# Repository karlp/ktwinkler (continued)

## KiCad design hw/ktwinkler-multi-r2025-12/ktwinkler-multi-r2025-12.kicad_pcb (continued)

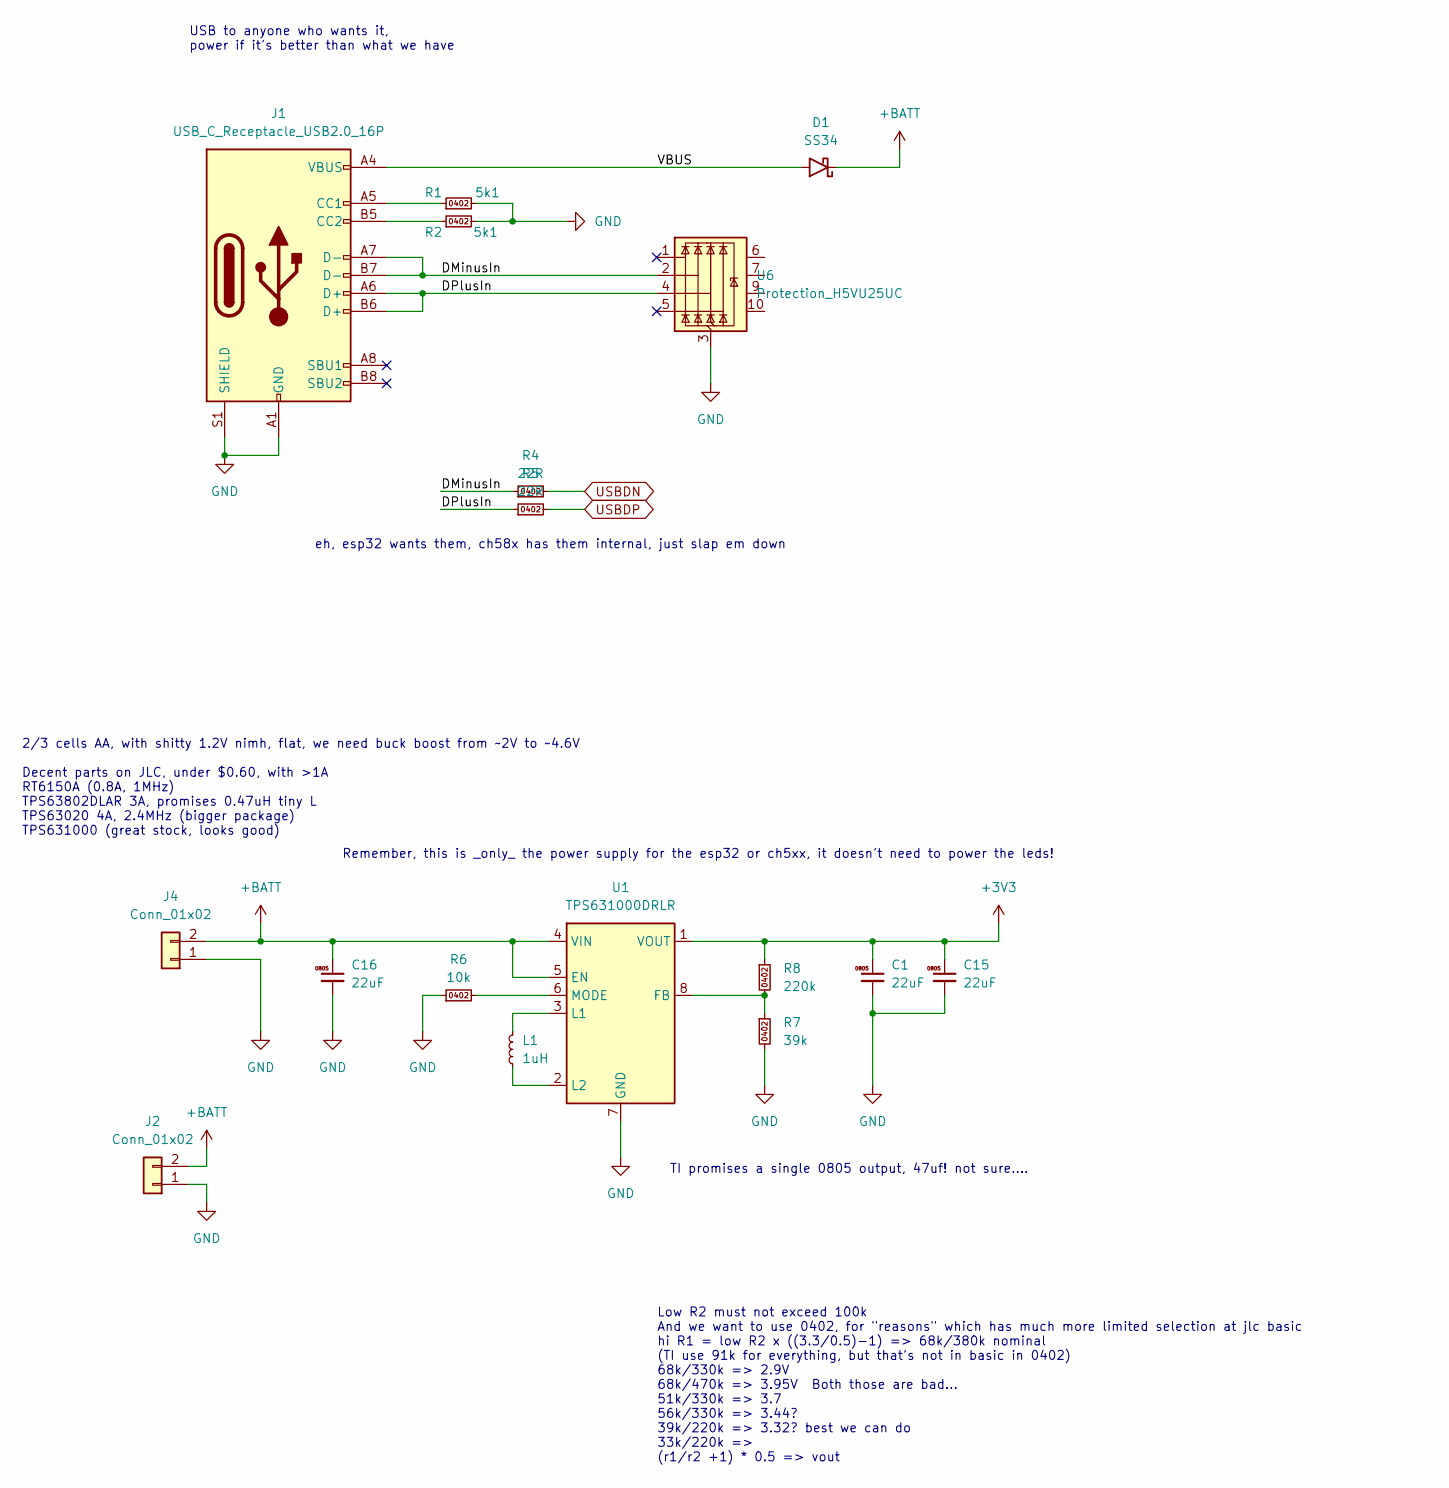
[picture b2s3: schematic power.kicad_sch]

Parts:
C1, C15, C16: 22uF; C_0805_2012Metric; MPN CL21A226MAQNNNE; LCSC Part # C45783
D1: SS34; D_SMA; MPN SS34; LCSC Part # C8678
J1: USB_C_Receptacle_USB2.0_16P; USB_C_Receptacle_GCT_USB4105-xx-A_16P_TopMnt_Horizontal; MPN GT-USB-7010ASV; LCSC Part # C2988369
J2: Conn_01x02; PinHeader_1x02_P2.54mm_Vertical
J4: Conn_01x02; PhoenixContact_MC_1,5_2-G-3.5_1x02_P3.50mm_Horizontal; MPN WJ15EDGVC-3.81-2P; LCSC Part # C8387
L1: 1uH; L_1206_3216Metric; MPN CMP321609UD1R0MT; LCSC Part # C139248
R1, R2: 5k1; R_0402_1005Metric; MPN 0402WGF5101TCE; LCSC Part # C25905
R4, R5: 22R; R_0402_1005Metric; MPN 0402WGF220JTCE; LCSC Part # C25092
R6: 10k; R_0402_1005Metric; MPN 0402WGF1002TCE; LCSC Part # C25744
R7: 39k; R_0402_1005Metric; MPN 0402WGF3902TCE; LCSC Part # C25783
R8: 220k; R_0402_1005Metric; MPN 0402WGF2203TCE; LCSC Part # C25767
U1: TPS631000DRLR; SOT-583-8; MPN TPS631000DRLR; LCSC Part # C5219190
U6: Protection_H5VU25UC; Diodes_UDFN-10_1.0x2.5mm_P0.5mm; MPN H5VU25UC; jlcbasic preferred

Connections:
+3V3: C1.1, C15.1, R8.1, U1.1 (VOUT); also elsewhere on the board
+BATT: C16.1, D1.1 (K), J2.2, J4.2, U1.4 (VIN), U1.5 (EN); also elsewhere on the board
/power/DMinusIn: J1.A7 (D-), J1.B7 (D-), R4.1, U6.2 (I/O2)
/power/DPlusIn: J1.A6 (D+), J1.B6 (D+), R5.1, U6.4 (I/O3)
/power/VBUS: D1.2 (A), J1.A4 (VBUS), J1.A9 (VBUS), J1.B4 (VBUS), J1.B9 (VBUS)
GND: C1.2, C15.2, C16.2, J1.A1 (GND), J1.A12 (GND), J1.B1 (GND), J1.B12 (GND), J1.S1 (SHIELD), J2.1, J4.1, R1.2, R2.2, R6.1, R7.2, U1.7 (GND), U6.3 (GND), U6.8 (GND); also elsewhere on the board
unnamed: J1.A5 (CC1), R1.1
unnamed: J1.B5 (CC2), R2.1
unnamed: R7.1, R8.2, U1.8 (FB)
unnamed: L1.2, U1.3 (L1)
unnamed: L1.1, U1.2 (L2)
unnamed: R6.2, U1.6 (MODE)
USBDN: R4.2; also elsewhere on the board
USBDP: R5.2; also elsewhere on the board

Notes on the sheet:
Low R2 must not exceed 100k And we want to use 0402, for "reasons" which has much more limited selection at jlc basic hi R1 = low R2 x ((3.3/0.5)-1) => 68k/380k nominal (TI use 91k for everything, but that's not in basic in 0402) 68k/330k => 2.9V 68k/470k => 3.95V Both those are bad... 51k/330k => 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
USB to anyone who wants it, power if it's better than what we have
2/3 cells AA, with shitty 1.2V nimh, flat, we need buck boost from ~2V to ~4.6V Decent parts on JLC, under $0.60, with >1A RT6150A (0.8A, 1MHz) TPS63802DLAR 3A, promises 0.47uH tiny L TPS63020 4A, 2.4MHz (bigger package) TPS631000 (great stock, looks good)
Remember, this is _only_ the power supply for the esp32 or ch5xx, it doesn't need to power the leds!
eh, esp32 wants them, ch58x has them internal, just slap em down
TI promises a single 0805 output, 47uf! not sure....

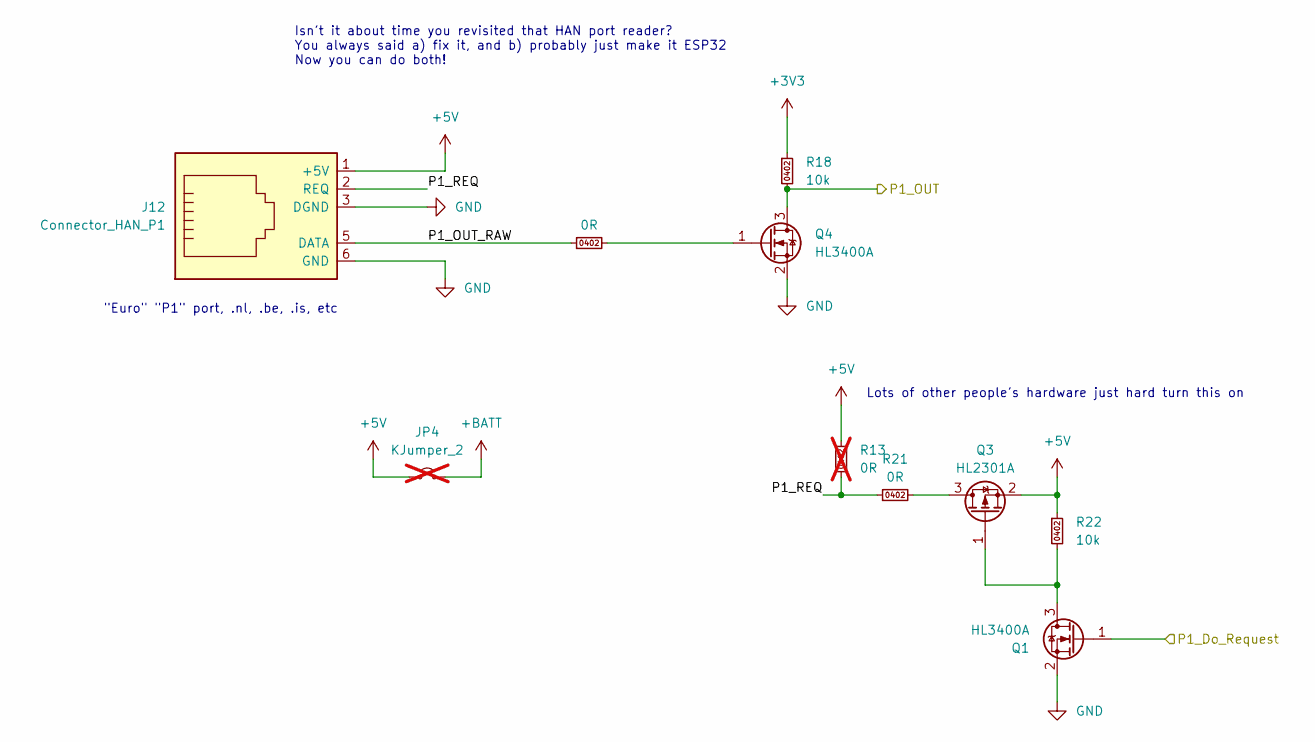
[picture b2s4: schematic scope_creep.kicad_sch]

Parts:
J12: Connector_HAN_P1; RJ25_Wayconn_MJEA-660X1_Horizontal; MPN R-RJ11R06P-A801
JP4: KJumper_2; TestPoint_2Pads_Pitch2.54mm_Drill0.8mm; not fitted
Q1, Q4: HL3400A; SOT-23; MPN HL3400A; LCSC Part # C7420348
Q3: HL2301A; SOT-23; jlcbasic preferred
R13: 0R; R_0402_1005Metric; MPN 0402WGF0000TCE; LCSC Part # C17168; not fitted
R17, R21: 0R; R_0402_1005Metric; MPN 0402WGF0000TCE; LCSC Part # C17168
R18, R22: 10k; R_0402_1005Metric; MPN 0402WGF1002TCE; LCSC Part # C25744

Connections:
+3V3: R18.1; also elsewhere on the board
+5V: J12.1 (+5V), JP4.1 (A), Q3.2 (S), R13.2, R22.1
+BATT: JP4.2 (B); also elsewhere on the board
/ScopeCreep/P1_OUT_RAW: J12.5 (DATA), R17.1
/ScopeCreep/P1_REQ: J12.2 (REQ), R13.1, R21.1
/ch584/PWM3: Q4.3 (D), R18.2; also elsewhere on the board
/ch584/PWM5: Q1.1 (G); also elsewhere on the board
GND: J12.3 (DGND), J12.6 (GND), Q1.2 (S), Q4.2 (S); also elsewhere on the board
unnamed: Q1.3 (D), Q3.1 (G), R22.2
unnamed: Q3.3 (D), R21.2
unnamed: Q4.1 (G), R17.2

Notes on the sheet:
Lots of other people's hardware just hard turn this on
Isn't it about time you revisited that HAN port reader? You always said a) fix it, and b) probably just make it ESP32 Now you can do both!
"Euro" "P1" port, .nl, .be, .is, etc

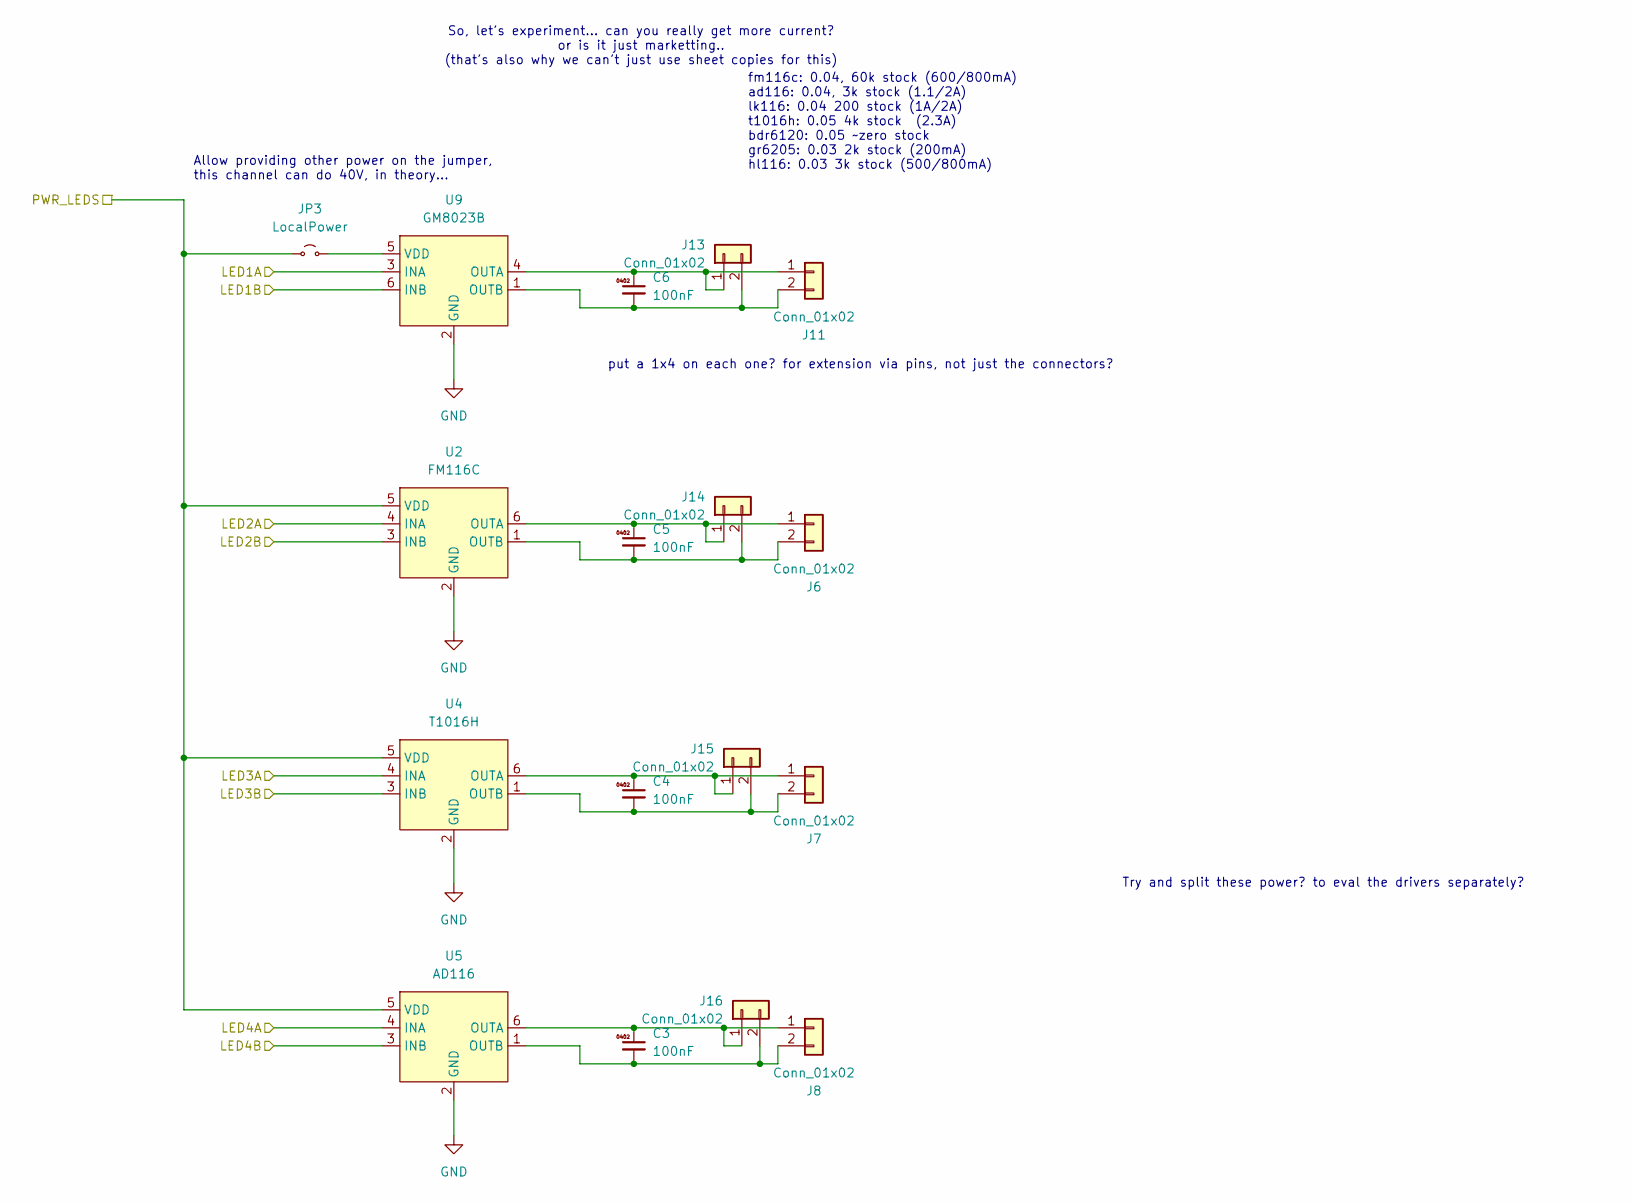
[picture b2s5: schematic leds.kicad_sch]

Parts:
C3, C4, C5, C6: 100nF; C_0402_1005Metric; MPN CL05B104KO5NNNC; LCSC Part # C1525
J6, J7, J8: Conn_01x02; PhoenixContact_MC_1,5_2-G-3.5_1x02_P3.50mm_Horizontal; MPN WJ15EDGVC-3.81-2P; LCSC Part # C8387
J11: Conn_01x02; PhoenixContact_MC_1,5_2-G-3.5_1x02_P3.50mm_Horizontal; MPN WJ15EDGRC-3.81-2P; LCSC Part # C8387
J13, J14, J15, J16: Conn_01x02; TestPoint_2Pads_Pitch2.54mm_Drill0.8mm
JP3: LocalPower; TestPoint_2Pads_Pitch2.54mm_Drill0.8mm
U2: FM116C; SOT-23-6; MPN FM116C; LCSC Part # C2802264
U4: T1016H; SOT-23-6; MPN T1016H; LCSC Part # C5142991
U5: AD116; SOT-23-6; MPN AD116; LCSC Part # C7463412
U9: GM8023B; SOT-23-6; MPN GM8023B; LCSC Part # C269871

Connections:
+BATT: JP3.1 (A), U2.5 (VDD), U4.5 (VDD), U5.5 (VDD); also elsewhere on the board
/ch584/PWM1: U9.3 (INA); also elsewhere on the board
/ch584/PWM2: U9.6 (INB); also elsewhere on the board
/ch584/PWM3: U2.4 (INA); also elsewhere on the board
/ch584/PWM4: U2.3 (INB); also elsewhere on the board
/ch584/PWM5: U4.4 (INA); also elsewhere on the board
/esp32/PWM7: U5.4 (INA); also elsewhere on the board
/esp32/PWM8: U5.3 (INB); also elsewhere on the board
GND: U2.2 (GND), U4.2 (GND), U5.2 (GND), U9.2 (GND); also elsewhere on the board
unnamed: C6.1, J11.1, J13.1, U9.4 (OUTA)
unnamed: C6.2, J11.2, J13.2, U9.1 (OUTB)
unnamed: C5.1, J6.1, J14.1, U2.6 (OUTA)
unnamed: C5.2, J6.2, J14.2, U2.1 (OUTB)
unnamed: C4.1, J7.1, J15.1, U4.6 (OUTA)
unnamed: C4.2, J7.2, J15.2, U4.1 (OUTB)
unnamed: C3.1, J8.1, J16.1, U5.6 (OUTA)
unnamed: C3.2, J8.2, J16.2, U5.1 (OUTB)
unnamed: JP3.2 (B), U9.5 (VDD)
RESET_CH5x: U4.3 (INB); also elsewhere on the board

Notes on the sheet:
So, let's experiment... can you really get more current? or is it just marketting.. (that's also why we can't just use sheet copies for this)
put a 1x4 on each one? for extension via pins, not just the connectors?
Allow providing other power on the jumper, this channel can do 40V, in theory...
Try and split these power? to eval the drivers separately?
fm116c: 0.04, 60k stock (600/800mA) ad116: 0.04, 3k stock (1.1/2A) lk116: 0.04 200 stock (1A/2A) t1016h: 0.05 4k stock (2.3A) bdr6120: 0.05 ~zero stock gr6205: 0.03 2k stock (200mA) hl116: 0.03 3k stock (500/800mA)

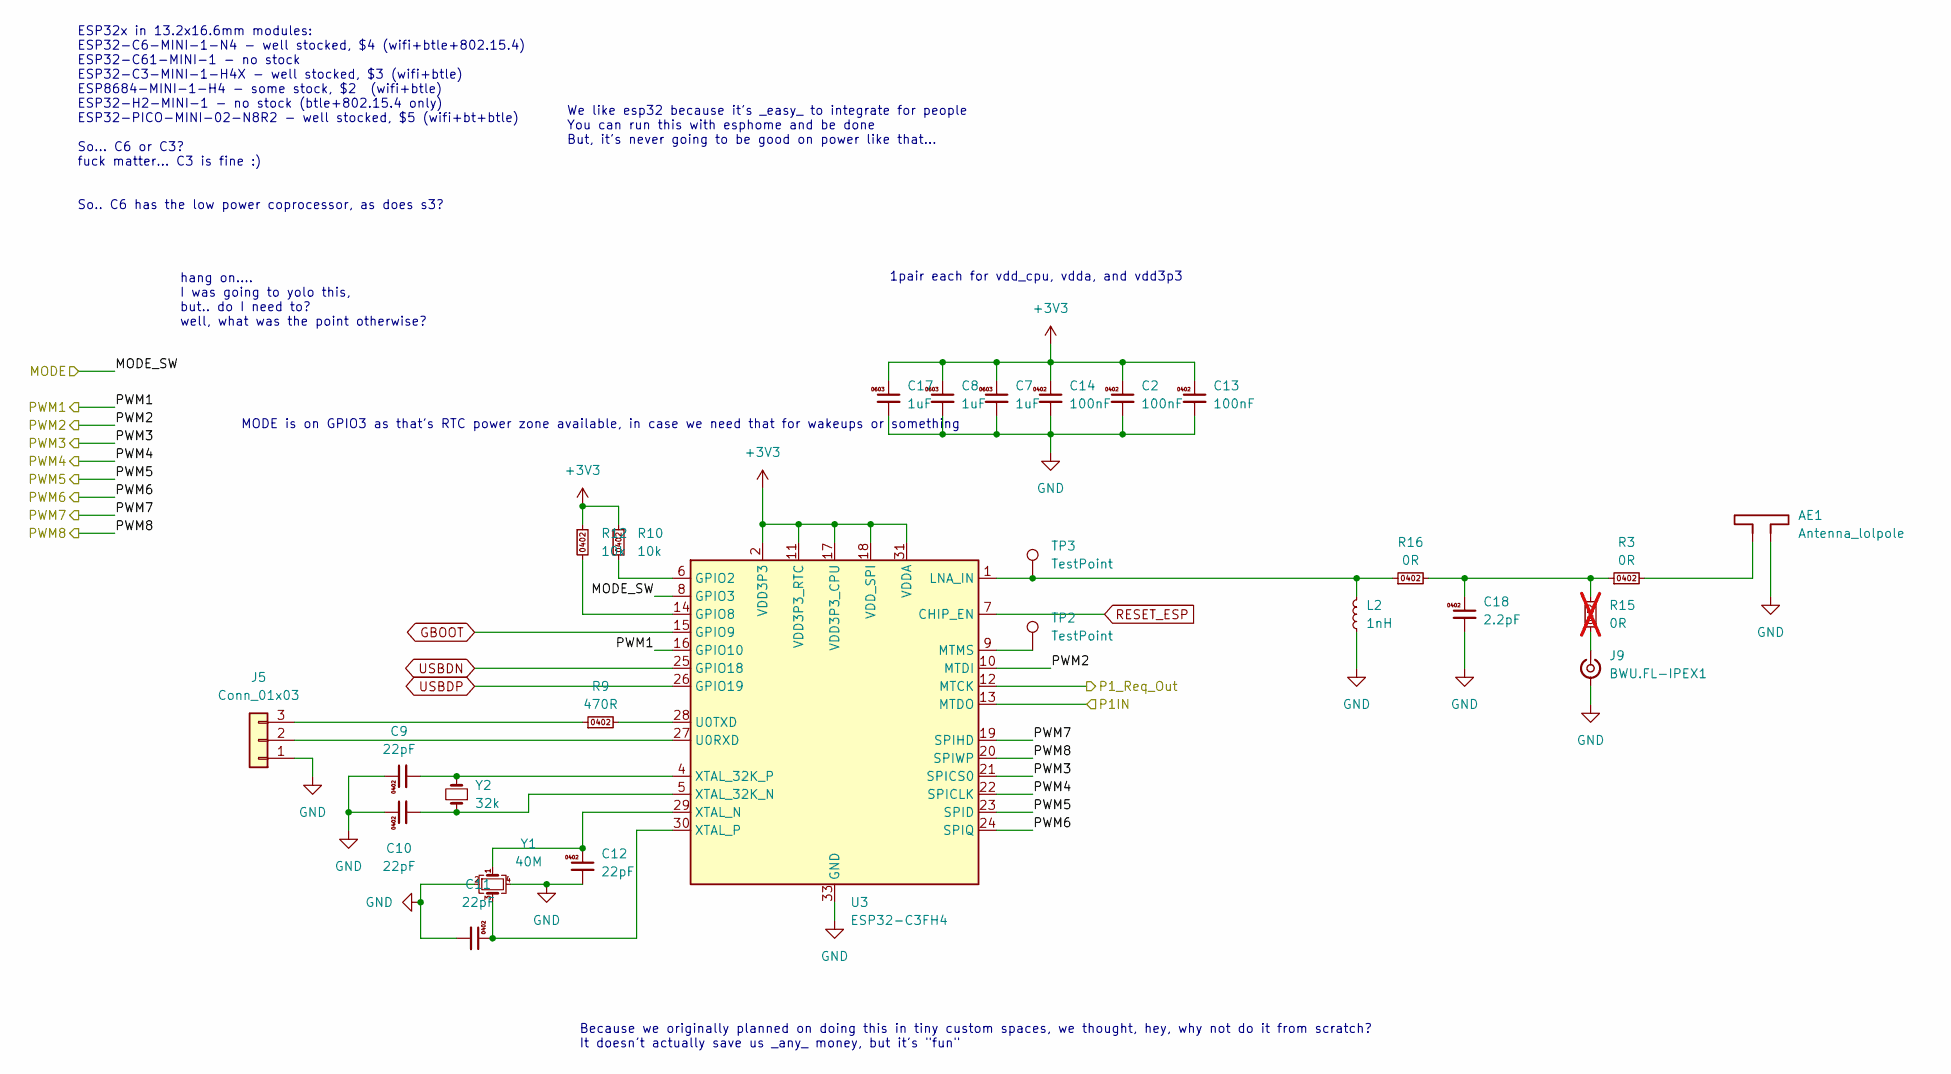
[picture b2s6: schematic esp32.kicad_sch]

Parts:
AE1: Antenna_lolpole; ANT-YOLOPOLE
C2, C13, C14: 100nF; C_0402_1005Metric; MPN CL05B104KO5NNNC; LCSC Part # C1525
C7, C8, C17: 1uF; C_0603_1608Metric; MPN CL10A105KB8NNNC; LCSC Part # C15849
C9, C10, C11, C12: 22pF; C_0402_1005Metric; MPN 0402CG220J500NT; LCSC Part # C1555
C18: 2.2pF; C_0402_1005Metric; MPN 0402CG2R2C500NT; LCSC Part # C1559
J5: Conn_01x03; PinHeader_1x03_P2.54mm_Vertical
J9: BWU.FL-IPEX1; U.FL_Hirose_U.FL-R-SMT-1_Vertical; MPN BWU.FL-IPEX1; LCSC Part # C5137195
L2: 1nH; L_0402_1005Metric; MPN LQG15HS1N0S02D; LCSC Part # C18222
R3, R16: 0R; R_0402_1005Metric; MPN 0402WGF0000TCE; LCSC Part # C17168
R9: 470R; R_0402_1005Metric; MPN 0402WGF4700TCE; LCSC Part # C25117
R10, R12: 10k; R_0402_1005Metric; MPN 0402WGF1002TCE; LCSC Part # C25744
R15: 0R; R_0402_1005Metric; MPN 0402WGF0000TCE; LCSC Part # C17168; not fitted
TP2: TestPoint; TestPoint_THTPad_D1.0mm_Drill0.5mm
TP3: TestPoint; TestPoint_Pad_D1.0mm
U3: ESP32-C3FH4; QFN-32-1EP_5x5mm_P0.5mm_EP3.7x3.7mm; MPN ESP32-C3FH4; LCSC Part # C2858491
Y1: 40M; Crystal_SMD_2016-4Pin_2.0x1.6mm; MPN TAXM40M4ZHBCDT2T; LCSC Part # C424432
Y2: 32k; Crystal_SMD_3215-2Pin_3.2x1.5mm; MPN Q13FC13500004; LCSC Part # C32346

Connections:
+3V3: C2.1, C7.1, C8.1, C13.1, C14.1, C17.1, R10.1, R12.1, U3.2 (VDD3P3), U3.3 (VDD3P3), U3.11 (VDD3P3_RTC), U3.17 (VDD3P3_CPU), U3.18 (VDD_SPI), U3.31 (VDDA), U3.32 (VDDA); also elsewhere on the board
/MODE: U3.8 (GPIO3); also elsewhere on the board
/ch584/PWM1: U3.16 (GPIO10); also elsewhere on the board
/ch584/PWM2: U3.10 (MTDI); also elsewhere on the board
/ch584/PWM3: U3.13 (MTDO), U3.21 (SPICS0); also elsewhere on the board
/ch584/PWM4: U3.22 (SPICLK); also elsewhere on the board
/ch584/PWM5: U3.12 (MTCK), U3.23 (SPID); also elsewhere on the board
/esp32/PWM7: U3.19 (SPIHD); also elsewhere on the board
/esp32/PWM8: U3.20 (SPIWP); also elsewhere on the board
GBOOT: U3.15 (GPIO9); also elsewhere on the board
GND: AE1.2, C2.2, C7.2, C8.2, C9.1, C10.1, C11.2, C12.2, C13.2, C14.2, C17.2, C18.2, J5.1, J9.2 (Ext), L2.1, U3.33 (GND), Y1.2, Y1.4; also elsewhere on the board
unnamed: AE1.1, R3.2
unnamed: C18.1, R3.1, R15.2, R16.2
unnamed: J5.2, U3.27 (U0RXD)
unnamed: J5.3, R9.1
unnamed: J9.1 (In), R15.1
unnamed: R10.2, U3.6 (GPIO2)
unnamed: R12.2, U3.14 (GPIO8)
unnamed: L2.2, R16.1, TP3.1 (1_1), U3.1 (LNA_IN)
unnamed: TP2.1 (1_1), U3.9 (MTMS)
unnamed: R9.2, U3.28 (U0TXD)
unnamed: C10.2, U3.5 (XTAL_32K_N), Y2.1
unnamed: C9.2, U3.4 (XTAL_32K_P), Y2.2
unnamed: C12.1, U3.29 (XTAL_N), Y1.1
unnamed: C11.1, U3.30 (XTAL_P), Y1.3
RESET_CH5x: U3.24 (SPIQ); also elsewhere on the board
RESET_ESP: U3.7 (CHIP_EN); also elsewhere on the board
USBDN: U3.25 (GPIO18); also elsewhere on the board
USBDP: U3.26 (GPIO19); also elsewhere on the board

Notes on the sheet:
hang on.... I was going to yolo this, but.. do I need to? well, what was the point otherwise?
MODE is on GPIO3 as that's RTC power zone available, in case we need that for wakeups or something
ESP32x in 13.2x16.6mm modules: ESP32-C6-MINI-1-N4 - well stocked, $4 (wifi+btle+802.15.4) ESP32-C61-MINI-1 - no stock ESP32-C3-MINI-1-H4X - well stocked, $3 (wifi+btle) ESP8684-MINI-1-H4 - some stock, $2 (wifi+btle) ESP32-H2-MINI-1 - no stock (btle+802.15.4 only) ESP32-PICO-MINI-02-N8R2 - well stoc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
Because we originally planned on doing this in tiny custom spaces, we thought, hey, why not do it from scratch? It doesn't actually save us _any_ money, but it's "fun"
We like esp32 because it's _easy_ to integrate for people You can run this with esphome and be done But, it's never going to be good on power like that...
1pair each for vdd_cpu, vdda, and vdd3p3

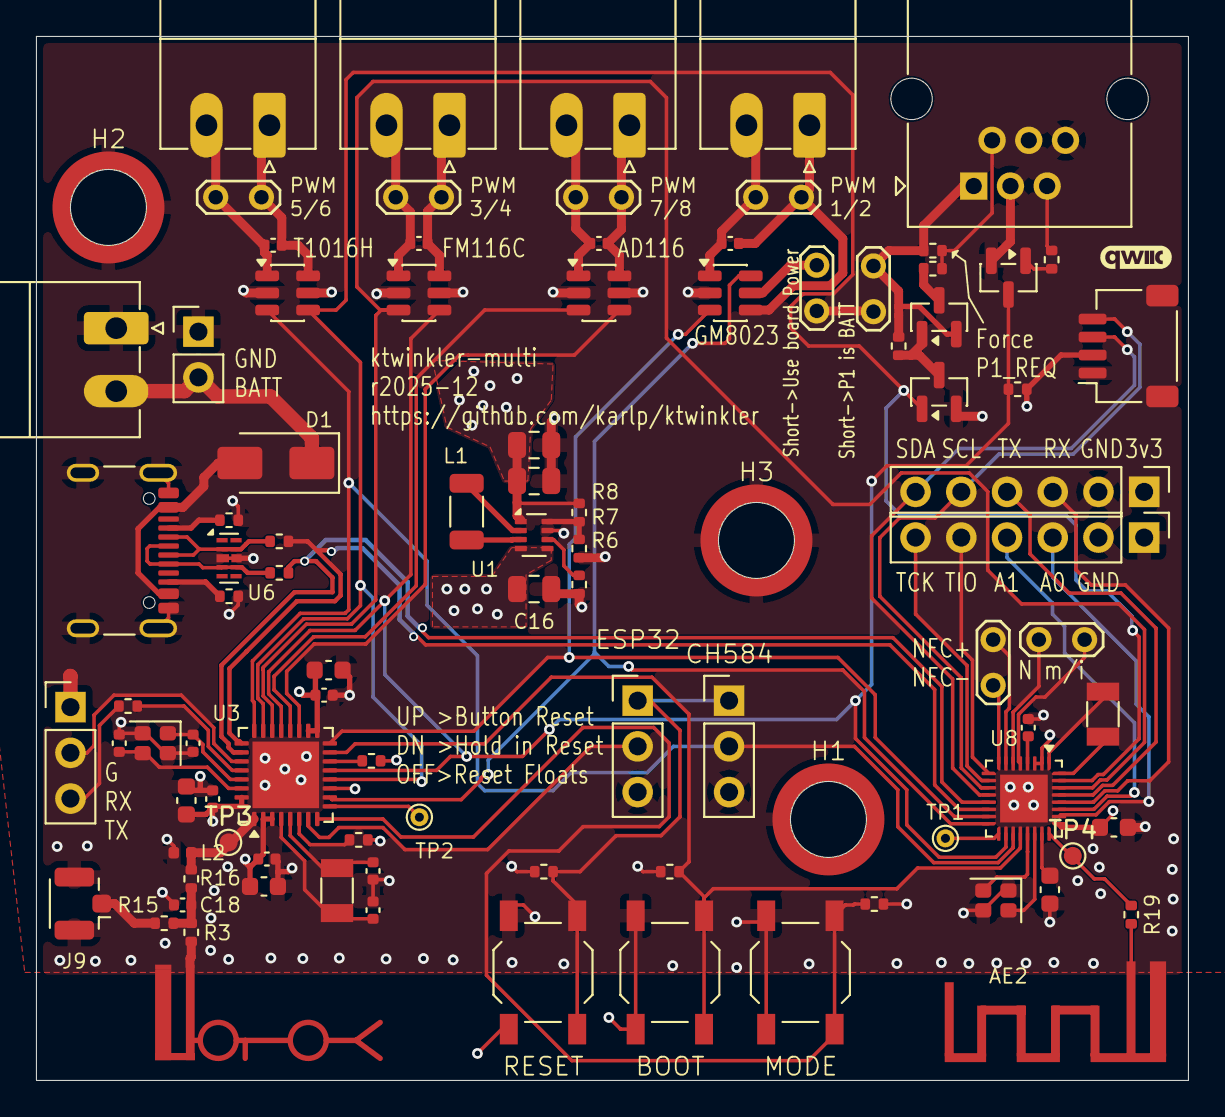
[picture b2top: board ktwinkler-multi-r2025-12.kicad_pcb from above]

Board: 4 copper layers, 64.0 x 58.0 mm, 97 parts (0 on the bottom side), 77 nets.

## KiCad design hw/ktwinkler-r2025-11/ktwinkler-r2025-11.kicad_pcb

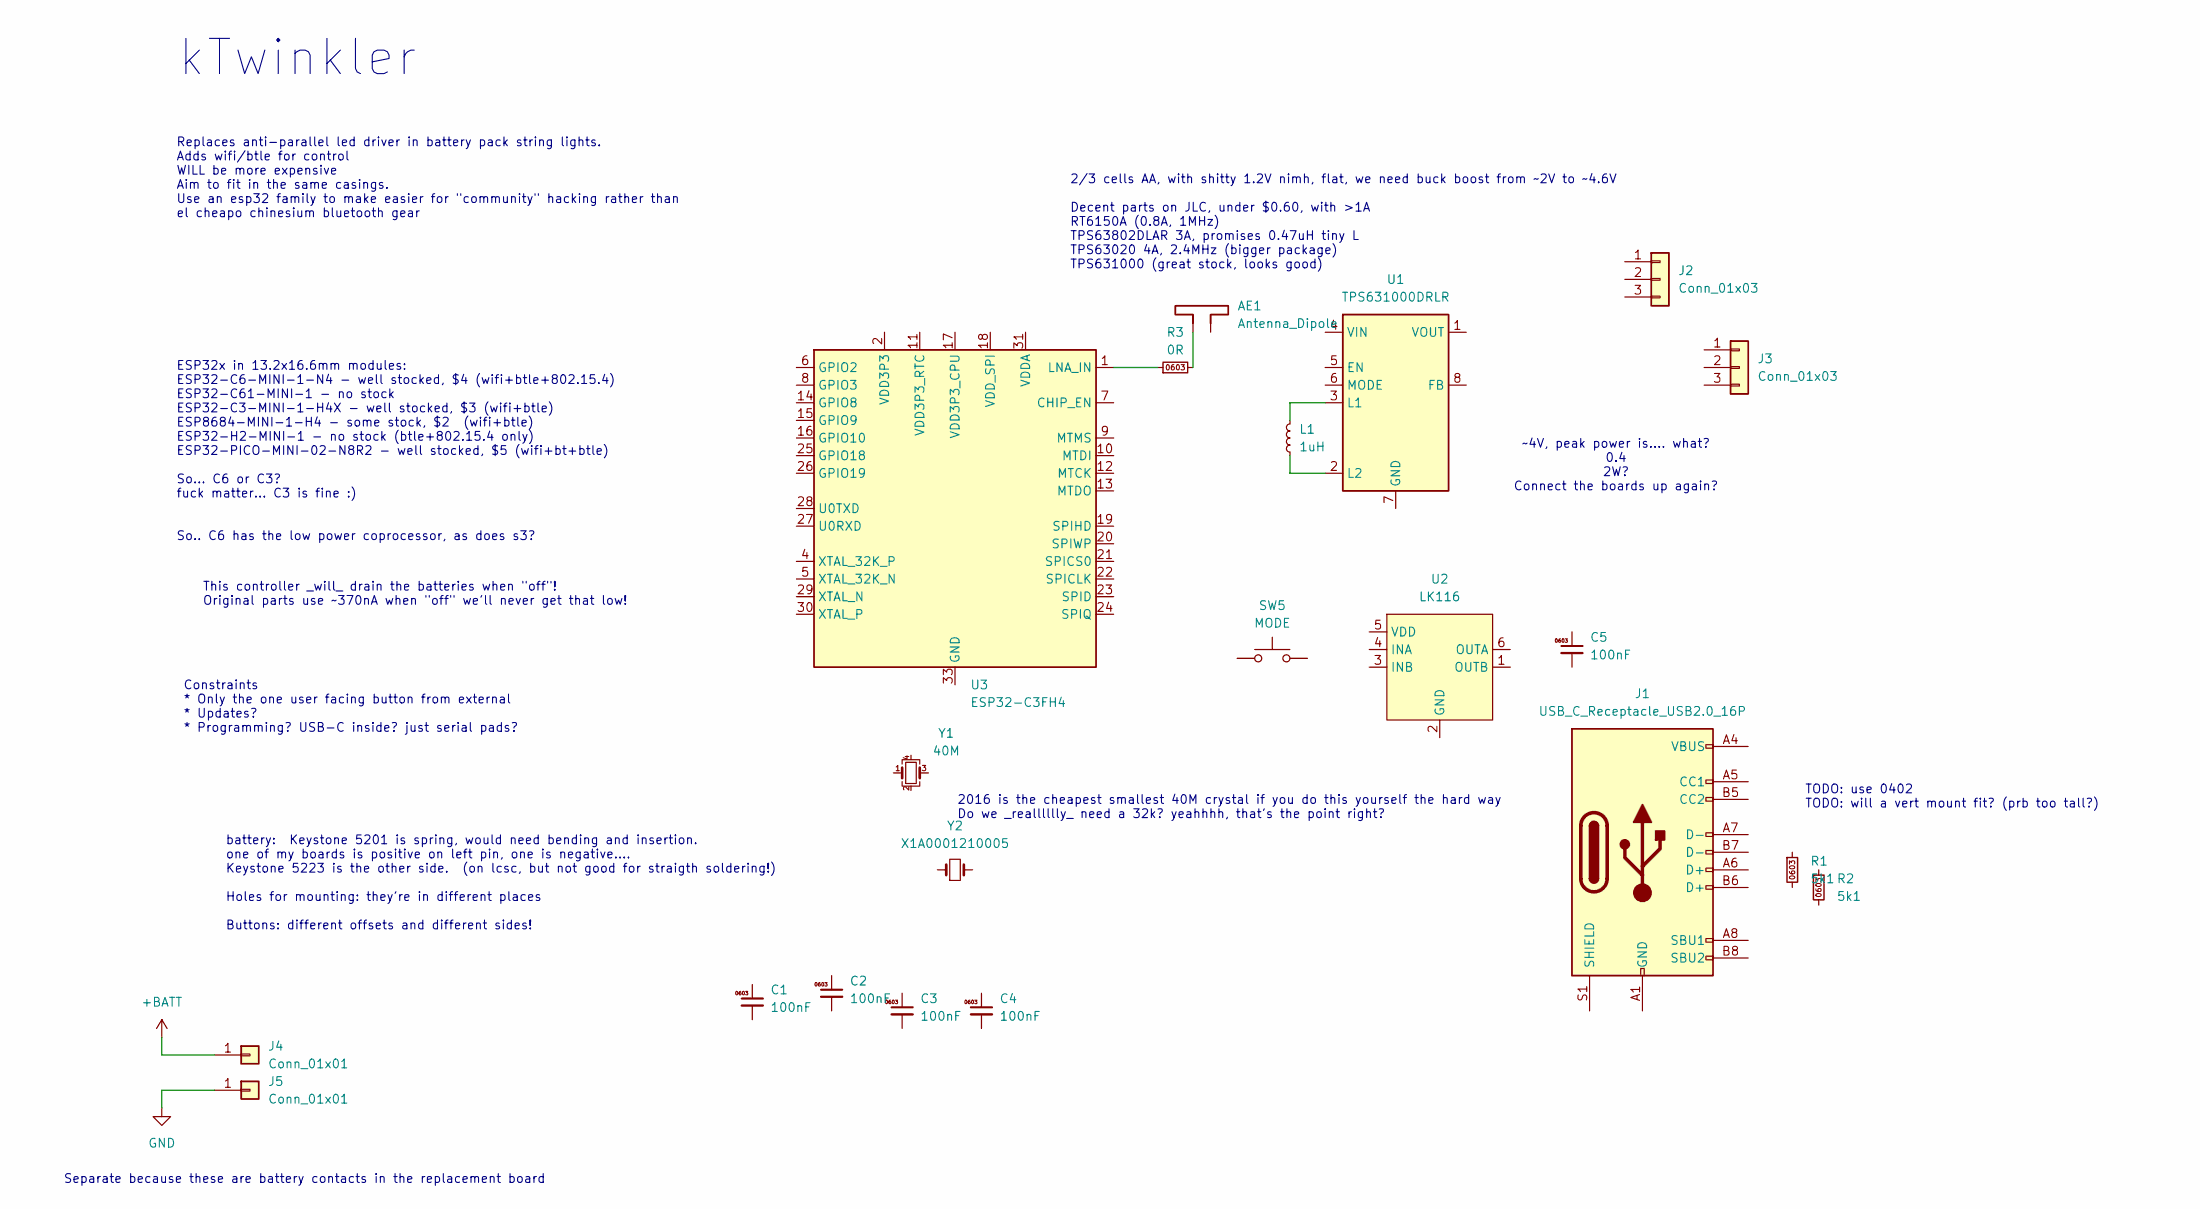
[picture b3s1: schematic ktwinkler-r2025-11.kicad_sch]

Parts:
AE1: Antenna_Dipole
C1, C2, C3, C4, C5: 100nF; C_0603_1608Metric; MPN CC0603KRX7R9BB104; LCSC Part # C14663
J1: USB_C_Receptacle_USB2.0_16P; USB_C_Receptacle_GCT_USB4110
J2: Conn_01x03; PinHeader_1x03_P2.54mm_Vertical
J3: Conn_01x03; TerminalBlock_Phoenix_MPT-0,5-3-2.54_1x03_P2.54mm_Horizontal
J4, J5: Conn_01x01; SolderWire-0.5sqmm_1x01_D0.9mm_OD2.1mm
L1: 1uH; L_1206_3216Metric; MPN CMP321609UD1R0MT; LCSC Part # C139248
R1, R2: 5k1; R_0603_1608Metric; MPN 0603WAF5101T5E; LCSC Part # C23186
R3: 0R; R_0603_1608Metric; MPN 0603WAF0000T5E; LCSC Part # C21189
SW5: MODE; SW_SPST_TL3342; MPN TS-1187A-B-A-B; jlcbasic basic
U1: TPS631000DRLR; SOT-583-8; MPN TPS631000DRLR; LCSC Part # C5219190
U2: LK116; SOT-23-6; MPN LK116; LCSC Part # C2984835
U3: ESP32-C3FH4; QFN-32-1EP_5x5mm_P0.5mm_EP3.7x3.7mm; MPN ESP32-C3FH4; LCSC Part # C2858491
Y1: 40M; Crystal_SMD_2016-4Pin_2.0x1.6mm
Y2: X1A0001210005; Crystal_SMD_MicroCrystal_CM9V-T1A-2Pin_1.6x1.0mm; MPN X1A0001210005; LCSC Part # C5154201

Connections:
+BATT: J4.1
GND: J5.1
unnamed: AE1.1, R3.2
unnamed: J1.A1 (GND), J1.A12 (GND), J1.B1 (GND), J1.B12 (GND)
unnamed: J1.A4 (VBUS), J1.A9 (VBUS), J1.B4 (VBUS), J1.B9 (VBUS)
unnamed: L1.2, U1.3 (L1)
unnamed: L1.1, U1.2 (L2)
unnamed: R3.1, U3.1 (LNA_IN)
unnamed: U3.2 (VDD3P3), U3.3 (VDD3P3)
unnamed: U3.31 (VDDA), U3.32 (VDDA)

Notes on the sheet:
Replaces anti-parallel led driver in battery pack string lights. Adds wifi/btle for control WILL be more expensive Aim to fit in the same casings. Use an esp32 family to make easier for "community" hacking rather than el cheapo chinesium bluetooth gear
2/3 cells AA, with shitty 1.2V nimh, flat, we need buck boost from ~2V to ~4.6V Decent parts on JLC, under $0.60, with >1A RT6150A (0.8A, 1MHz) TPS63802DLAR 3A, promises 0.47uH tiny L TPS63020 4A, 2.4MHz (bigger package) TPS631000 (great stock, looks good)
kTwinkler
TODO: use 0402 TODO: will a vert mount fit? (prb too tall?)
Constraints * Only the one user facing button from external * Updates? * Programming? USB-C inside? just serial pads?
2016 is the cheapest smallest 40M crystal if you do this yourself the hard way Do we _realllllly_ need a 32k? yeahhhh, that's the point right?
~4V, peak power is.... what? 0.4 2W? Connect the boards up again?
battery: Keystone 5201 is spring, would need bending and insertion. one of my boards is positive on left pin, one is negative.... Keystone 5223 is the other side. (on lcsc, but not good for straigth soldering!) Holes for mounting: they're in different places Buttons: different offsets and different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
Separate because these are battery contacts in the replacement board
This controller _will_ drain the batteries when "off"! Original parts use ~370nA when "off" we'll never get that low!
ESP32x in 13.2x16.6mm modules: ESP32-C6-MINI-1-N4 - well stocked, $4 (wifi+btle+802.15.4) ESP32-C61-MINI-1 - no stock ESP32-C3-MINI-1-H4X - well stocked, $3 (wifi+btle) ESP8684-MINI-1-H4 - some stock, $2 (wifi+btle) ESP32-H2-MINI-1 - no stock (btle+802.15.4 only) ESP32-PICO-MINI-02-N8R2 - well stoc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

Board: 2 copper layers, 20 parts (0 on the bottom side), 7 nets, no tracks yet.

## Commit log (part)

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2025-11-05 let's goooo
2025-11-17 pushing ideas around
2025-11-17 test mpy code to verify that it works
    ran this with the antiparallel led strips driven by drv8833.
    should be fine with ~any cheap 1ch driver too.
2025-12-02 import draft play as a new board
2025-12-02 make a v2 idea, mroe experiments, less product...
2025-12-04 ktwinkler hw dev: progress stash
2025-12-09 pushing onwards like a madlad
2025-12-11 ready for scope creep
    I think the schematic is ... mostly ok? I need to decide how much of
    the han p1 port scope creep to bother doing, or not...
    I've roughyl blocked out the board, seems as good as any?
2025-12-16 this is just getting silly
2025-12-18 "schematic complete" (lol)
    but yeah, i think this is most of it? time to maybe route shit?
2025-12-25 update following ERC and symbol fixes
2025-12-25 streammmm updates
    "complete" apart from finishing those antennas.
    needs DRC cleanups on both the wch inv-f and also the yolo-pole.
    need to at least _basically_ get the antenna trace basic wdith correct
    as well. yolo is fine, when it's guided yolo, not "lol"
2025-12-28 stuff
2025-12-28 more scribble
2026-01-09 attempting to progres towards a build
2026-03-10 first play PIFA sim
    Adds the 2.2 demos, emerge did a major release while we were
    daydreaming.
    Adds our very initial PIFA sim, which is not at all complete, but, it's
    a start. Adds a kicad footprint, we eventually want to turn a kicad
    footprint into an emerge model "automagically" for this sort of
    thing....
2026-03-11 scifi continues...
2026-03-24 drop fp-info-cache from git
2026-03-24 hw: save before kicad 10 upgrade
2026-03-24 hw: update to kicad 10 and order
    We added a late qwiic connector to the ch584 side, why not, try that out
    too. We also fixed our smtso footprint, we hope...
    Fuck poking the rf more, we're yolo-poling...
2026-04-19 hw/ktwinkler-multi: fix the bi/uni tvs fuckup
    We're not likely to make a new version of _exactly_ this board, but
    don't leave the totally busted short circuit around to stumble on later!
2026-04-20 add micropython submodule for firmware
2026-04-20 hw/multi-rev2025: flag more total fuckups in the design
    lol, using 6 PWMs on the internal spi channel. I've read that section
    multiple times, and just... wot? oh well. Cut a few traces, can still
    do some things...
2026-04-20 fw: move proto twinkle to fw src
    And update for the only functional pwm pins on current hw, for esp32
    side at least.
2026-04-20 Add micropython board definition for esp32 side
